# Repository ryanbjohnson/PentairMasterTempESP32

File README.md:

# Pentair MasterTemp ESP32 Interface

Open hardware and firmware-planning repository for a draft ESP32-based operating-control interface for the Pentair MasterTemp 125 heater family.

This project is early-stage engineering work. It is not a finished product, not certified, and not approved for connection to a live gas appliance.

## Safety First

- Read [DISCLAIMER.md](DISCLAIMER.md) before using any design file in this repository.
- Do not route or apply line voltage on this PCB.
- Do not add any ESP32-controlled gas-valve output.
- Preserve the OEM ignition control module and its sequencing.
- Keep the heat-request path fail-open with two normally-open relay contacts in series unless a qualified safety review approves a different architecture.
- Treat Wi-Fi, MQTT, Home Assistant, and firmware commands as advisory only. They must never override safety faults.
- A qualified technician and controls/electrical safety reviewer must approve any live-heater test.

## Current Status

The repository currently contains a KiCad scaffold and first-pass schematic capture for major control-board blocks:

- 24 VAC power entry and low-voltage rails.
- Operating-control/ICM interface and dual relay heat-request chain.
- ESP32 supervisor, watchdog, brownout, and relay-gate contract.
- Manual-aligned safety-stack input sheet and static safety gate.
- Field verification and OEM-board photo layout notes.

Remaining work includes final schematic capture, field verification, PCB/schematic parity cleanup, routing, FMEA, bench validation, and professional safety review.

## Repository Map

- `MasterTemp_ESP32_Interface_Preliminary_Design.md`: top-level design intent and safety boundary.
- `pcb/mastertemp_esp32/`: KiCad project.
- `pcb/mastertemp_esp32/docs/`: design notes, manual review, field verification, and layout notes.
- `pcb/mastertemp_esp32/references/`: project-local manuals and visual references used during review.
- `pcb/requirements/`: machine-readable requirements.
- `scripts/`: headless KiCad and test automation.
- `tests/`: scaffold and safety-boundary regression tests.

## Development Quick Start

Install KiCad 8 and Python 3, or use the included dev container.

Run checks:

```bash
./scripts/run-tests.sh
./scripts/kicad-check.sh
```

Open the KiCad project:

```bash
pcb/mastertemp_esp32/mastertemp_esp32.kicad_pro
```

Generated outputs go in ignored `reports/` and `fab/` directories.

## Contributing

Read [CONTRIBUTING.md](CONTRIBUTING.md) before opening issues or pull requests. Contributions that weaken the safety boundary, directly drive the gas valve, add line-voltage routing, or bypass the OEM ignition control module will not be accepted.

Useful first contributions:

- Improve field-verification checklists and documentation.
- Capture missing schematic detail with clear review stubs where assumptions remain open.
- Reduce ERC/DRC/parity issues without masking safety problems.
- Improve tests that enforce the safety boundary.
- Review connector pinout assumptions against installed-heater evidence.

## Security And Safety Reports

Report safety or security issues using GitHub private vulnerability reporting when available, or follow [SECURITY.md](SECURITY.md). Do not publish exploit steps, unsafe bypass instructions, or live-appliance test procedures in public issues.

## License

This repository is licensed under the MIT License. See [LICENSE](LICENSE).

Before first public hardware release, the project owner may choose to move hardware design files to a hardware-specific license such as CERN-OHL-S-2.0; see [docs/licensing.md](docs/licensing.md).

## Publishing Checklist

Before making the repository public or tagging a release, review [docs/open_source_release_checklist.md](docs/open_source_release_checklist.md).

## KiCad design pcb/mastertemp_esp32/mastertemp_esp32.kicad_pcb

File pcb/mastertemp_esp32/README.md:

# MasterTemp ESP32 KiCad Scaffold

This folder is the KiCad project area for the MasterTemp 125 ESP32 interface board.

The current files are a scaffold, not a completed schematic or board layout. The design intent and safety constraints live in:

- `../../MasterTemp_ESP32_Interface_Preliminary_Design.md`
- `../requirements/mastertemp_esp32_requirements.yaml`

Installed-heater inputs required before electrical release are tracked in `docs/field_input_verification.md`.

The original Pentair board photo reference is tracked in `docs/oem_board_photo_layout_notes.md`; save the image itself as `references/images/original_pentair_control_board_front.jpg` when exporting the chat/IDE attachment.

## Recommended workflow

1. Open `mastertemp_esp32.kicad_pro` in KiCad.
2. Immediately save the project from KiCad once, so your installed KiCad version normalizes the project metadata.
3. Work sheet by sheet, starting with `sheets/power_24vac.kicad_sch`.
4. After each sheet-level change, run ERC.
5. After placement/routing changes, run DRC.
6. Keep all project-local symbols in `libraries/symbols/mastertemp_esp32.kicad_sym`.
7. Keep all project-local footprints in `libraries/footprints/mastertemp_esp32.pretty`.

## Safety notes

- This project is an operating-control interface only.
- Do not add any ESP32-controlled gas-valve output.
- Do not route line voltage on this PCB.
- Preserve the OEM ignition control module and its sequencing.
- The heat-request output must remain dual normally-open relay contacts in series unless a qualified safety review approves another architecture.

## Folder map

- `sheets/`: hierarchical schematic sheets.
- `libraries/`: project-local symbols and footprints.
- `rules/`: layout constraints and DRC notes.
- `docs/`: design workflow notes, pin maps, and review records.
- `references/`: project-local manuals, source documents, and non-release visual references.

## Completion checklist

Use this as the live gate list for moving from scaffold to a reviewable PCB package. Keep each checkbox honest: complete means captured, checked, and reviewed, not merely started.

### Project setup

- [x] KiCad project scaffold exists with root schematic, child sheets, PCB file, local library tables, and scripts.
- [x] Four-layer board scaffold exists with preliminary 160 mm x 100 mm outline and functional placement zones.
- [x] PCB floorplan v0 exists with connector, relay, power, ESP32, analog, and test-pad placement envelopes.
- [x] Local MasterTemp 125 Rev C PDF electrical pages were reviewed and summarized in `docs/mastertemp125_rev_c_manual_review.md`.
- [x] Candidate sourced BOM and first-pass footprint placement exist for control-board circuitry.
- [x] PCB-side draft nets and first-pass relay contact-chain routing are applied and documented.
- [x] Headless KiCad `ERC` and `DRC` automation runs in the dev container.
- [x] Repository-level scaffold tests exist under `tests/`.
- [ ] KiCad project metadata has been opened and normalized once in the target GUI KiCad version.
- [ ] Generated `reports/` and `fab/` outputs are regenerated from the final release candidate.

### Inputs to close before electrical release

- [ ] Exact MasterTemp 125 model revision, serial/date range, and connected/non-connected variant are recorded.
- [ ] Field input verification record is complete and reviewed in `docs/field_input_verification.md`.
- [x] Rev C manual connector groups are reflected in draft requirements and floorplan.
- [ ] Heater harness pinout is verified from the installed unit and matching manual revision.
- [ ] 24 VAC transformer no-load and loaded voltages are measured.
- [ ] Water thermistor resistance curve is confirmed.
- [ ] Stack flue sensor electrical type and valid/fault ranges are confirmed.
- [ ] Enclosure, mounting holes, standoff height, cable-entry direction, and service clearances are selected.
- [ ] Certification/review path is chosen, including current applicable pool-heater and automatic-control standards.

### Schematic capture

- [ ] `power_24vac`: connector, fuse/PTC, MOV/TVS, bridge, VRAW bulk, 5 V supply, 3.3 V supply, power-good/brownout.
- [ ] `icm_interface`: manual-aligned operating-control connector, dual series normally-open relay contacts, coil drivers, flyback, AC opto sense, TH feedback, ICM terminal reference.
- [ ] `esp32_supervisor`: ESP32 module, programming header, watchdog, reset supervisor, I2C, relay-enable logic.
- [ ] `safety_inputs`: Fireman's Switch, PS, HLS, ES1, AGS static chain, AFS dynamic monitor, dry-contact isolated sense.
- [ ] `thermistor_sfs`: first-pass ADC/window-comparator architecture captured; final thermistor/SFS values and thresholds remain field-open.
- [ ] `ui_remote`: Pool/Common/Spa external-control dry-contact sense only; keypad/display/buzzer/status LED design remains out of scope.
- [ ] ERC has zero unreviewed violations after each sheet is captured.
- [ ] All symbols have footprints assigned or documented as no-fit/test-only.

### Safety review

- [ ] OEM ignition control module remains responsible for ignition, flame proving, and gas-valve sequencing.
- [ ] No ESP32 or board output can directly energize the gas valve.
- [ ] No line-voltage nets, connectors, labels, or routing exist on this PCB.
- [ ] Two normally-open relay contacts are in series in the `TH` heat-request path.
- [ ] Relay drive drops out on ESP32 reset, watchdog timeout, brownout, firmware fault, OTA, static safety open, invalid sensor, and relay feedback fault.
- [ ] AFS is treated as a dynamic airflow-proving input, not as a static pre-fire interlock.
- [ ] Preliminary FMEA covers welded relay, optocoupler failure, stuck ADC, brownout oscillation, firmware deadlock, and miswire cases.

### PCB layout

- [x] First-pass placement envelopes follow the zone plan in `rules/layout_constraints.md`.
- [x] Draft connector envelopes follow Rev C Figure 24 operating-control groups.
- [x] Candidate footprints are placed according to first-pass sourced part numbers.
- [x] Critical relay contact-chain PCB nets are named and first-pass routed.
- [ ] Footprints are synchronized to final schematic symbols and netlist.
- [x] ESP32 antenna keepout has no copper, components, or nearby metal-obstructing placement in the draft placement.
- [ ] Relay contact and 24 VAC control paths use assigned net classes and visible separation from logic.
- [ ] Field-side optocoupler pins face connectors and logic-side pins face MCU/expander circuitry.
- [ ] Thermistor/SFS analog traces avoid relay coils, AC sense, ESD discharge paths, and buck switch nodes.
- [x] Test pads exist for `VRAW`, `+5V`, `+3V3`, watchdog, safety chain, relay coils, TH feedback, and VAL sense.
- [x] Silkscreen warnings are present and readable.
- [x] DRC has zero unreviewed violations and schematic parity passes for the current draft.

### Fabrication and validation

- [ ] Schematic PDF, PCB plots, Gerbers, drill files, BOM, and placement outputs are generated.
- [ ] Bench test procedure is executed with an isolated 24 VAC transformer.
- [ ] Every required heat-request drop-out case is tested and recorded.
- [ ] Relay feedback/welded-contact detection is tested.
- [ ] `VAL` sense-only behavior is tested.
- [ ] 24-hour relay/sensor soak test is completed.
- [ ] Qualified technician review is complete before any live-heater connection.

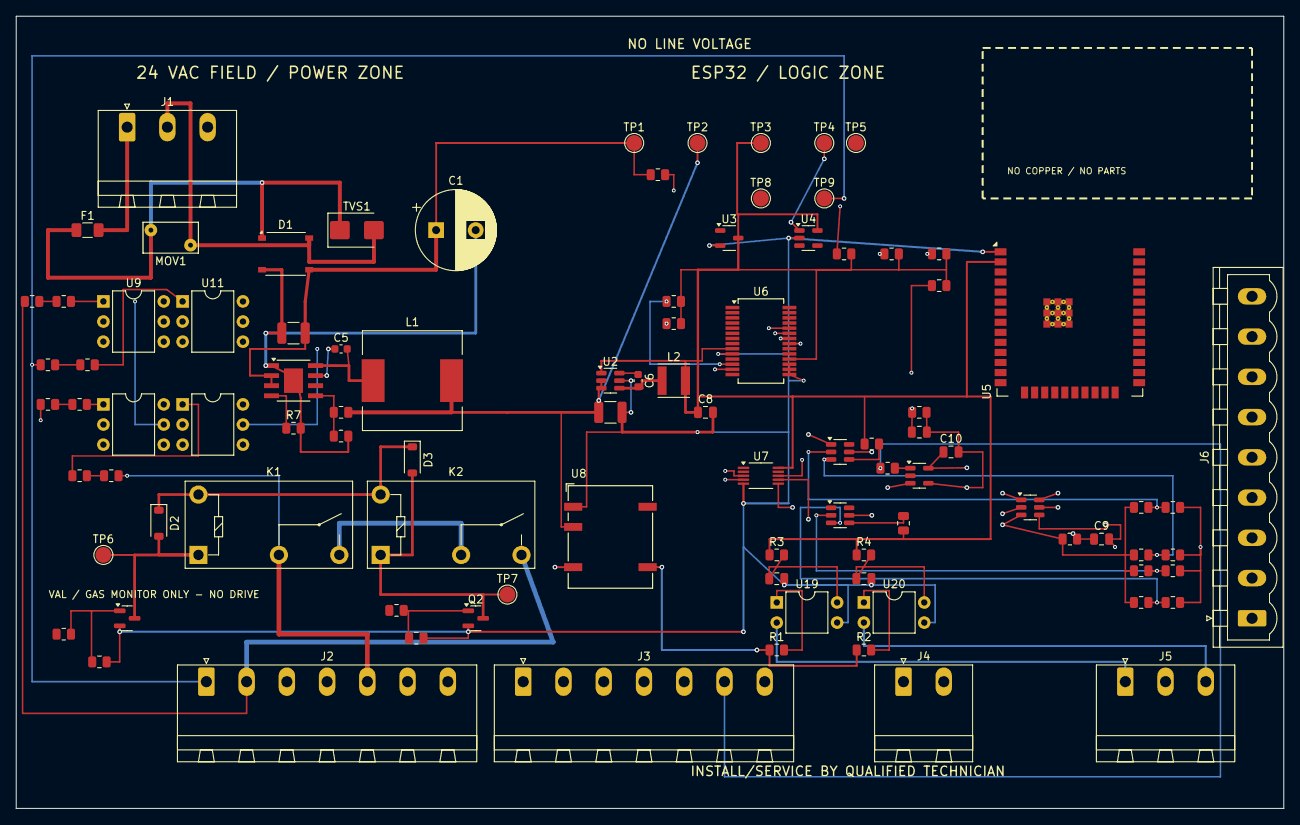
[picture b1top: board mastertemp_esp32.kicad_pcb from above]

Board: 4 copper layers, 160.0 x 100.0 mm, 95 parts (0 on the bottom side), 64 nets.

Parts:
C1: 470uF_63V; CP_Radial_D10.0mm_P5.00mm
C2, C3: 100nF_REMOTE_FILTER_TBD; C_0805_2012Metric
C4: 2.2uF_100V_VRAW_IN_TBD; C_1210_3225Metric
C5: 2.2nF_50V_BST_5V; C_0603_1608Metric
C6: 100nF_BST_3V3; C_0603_1608Metric
C7: 10uF_50V_3V3_IN_TBD; C_1210_3225Metric
C8: 22uF_10V_3V3_OUT_TBD; C_0805_2012Metric
C9: THERM_ADC_FILTER_TBD; C_0805_2012Metric
C10: SFS_ADC_FILTER_TBD; C_0805_2012Metric
C11: VRAW_MON_FILTER_TBD; C_0805_2012Metric
D1: MB10S; Diode_Bridge_Vishay_MBLS
D2: K1_FLYBACK_TBD; D_SOD-123
D3: K2_FLYBACK_TBD; D_SOD-123
F1: 0.5A_FUSE; Fuse_1206_3216Metric
J1: 24VAC_IN; PhoenixContact_MSTBA_2,5_3-G-5,08_1x03_P5.08mm_Horizontal
J2: OPERATING_CONTROL; PhoenixContact_MSTBA_2,5_7-G-5,08_1x07_P5.08mm_Horizontal
J3: SAFETY_STACK; PhoenixContact_MSTBA_2,5_7-G-5,08_1x07_P5.08mm_Horizontal
J4: THERMISTOR; PhoenixContact_MSTBA_2,5_2-G-5,08_1x02_P5.08mm_Horizontal
J5: EXT_CONTROL; PhoenixContact_MSTBA_2,5_3-G-5,08_1x03_P5.08mm_Horizontal
J6: MEMBRANE_REF; PhoenixContact_MSTBVA_2,5_9-G-5,08_1x09_P5.08mm_Vertical
K1, K2: G5Q-1A-DC5; Relay_SPST_Omron-G5Q-1A
L1: 68uH; L_12x12mm_H8mm
L2: 2.2uH; L_Vishay_IFSC-1515AH_4x4x1.8mm
MOV1: V47ZA1P; RV_Disc_D7mm_W3.9mm_P5mm
Q1, Q2: AO3400A; SOT-23
R1, R2: 2.2k_REMOTE_WET_TBD; R_0805_2012Metric
R3, R4: 10k_REMOTE_PULLUP; R_0805_2012Metric
R5: RFB5V_TOP_TBD; R_0805_2012Metric
R6: RFB5V_BOT_TBD; R_0805_2012Metric
R7: RON5V_TBD; R_0805_2012Metric
R8: VAL_OPTO_LIMIT_A_TBD; R_0805_2012Metric
R9: VAL_OPTO_LIMIT_B_TBD; R_0805_2012Metric
R10: K1_GATE_PULLDOWN_TBD; R_0805_2012Metric
R11: K2_GATE_PULLDOWN_TBD; R_0805_2012Metric
R12: VAL_OPTO_PULLUP_TBD; R_0805_2012Metric
R13: TH_OPTO_LIMIT_A_TBD; R_0805_2012Metric
R14: TH_OPTO_LIMIT_B_TBD; R_0805_2012Metric
R15: TH_OPTO_PULLUP_TBD; R_0805_2012Metric
R16: IND_OPTO_LIMIT_A_TBD; R_0805_2012Metric
R17: IND_OPTO_LIMIT_B_TBD; R_0805_2012Metric
R18: IND_OPTO_PULLUP_TBD; R_0805_2012Metric
R19: VAC24_OPTO_LIMIT_A_TBD; R_0805_2012Metric
R20: VAC24_OPTO_LIMIT_B_TBD; R_0805_2012Metric
R21: VAC24_OPTO_PULLUP_TBD; R_0805_2012Metric
R22: K1_GATE_SERIES_TBD; R_0805_2012Metric
R23: K2_GATE_SERIES_TBD; R_0805_2012Metric
R24: THERM_PULLUP_TBD; R_0805_2012Metric
R25: I2C_SDA_PULLUP_TBD; R_0805_2012Metric
R26: I2C_SCL_PULLUP_TBD; R_0805_2012Metric
R27: SFS_INPUT_SERIES_TBD; R_0805_2012Metric
R28: VRAW_MON_TOP_TBD; R_0805_2012Metric
R29: VRAW_MON_BOT_TBD; R_0805_2012Metric
R30: THERM_RANGE_OK_PULLUP_TBD; R_0805_2012Metric
R31: SFS_RANGE_OK_PULLUP_TBD; R_0805_2012Metric
R32: THERM_LOW_REF_TOP_TBD; R_0805_2012Metric
R33: THERM_LOW_REF_BOT_TBD; R_0805_2012Metric
R34: THERM_HIGH_REF_TOP_TBD; R_0805_2012Metric
R35: THERM_HIGH_REF_BOT_TBD; R_0805_2012Metric
R36: SFS_LOW_REF_TOP_TBD; R_0805_2012Metric
R37: SFS_LOW_REF_BOT_TBD; R_0805_2012Metric
R38: SFS_HIGH_REF_TOP_TBD; R_0805_2012Metric
R39: SFS_HIGH_REF_BOT_TBD; R_0805_2012Metric
TP1: VRAW; TestPoint_Pad_D2.0mm
TP2: +5V; TestPoint_Pad_D2.0mm
TP3: +3V3; TestPoint_Pad_D2.0mm
TP4: WATCHDOG_OK; TestPoint_Pad_D2.0mm
TP5: SAFETY_STATIC_OK; TestPoint_Pad_D2.0mm
TP6: K1_COIL; TestPoint_Pad_D2.0mm
TP7: K2_COIL; TestPoint_Pad_D2.0mm
TP8: TH_FEEDBACK; TestPoint_Pad_D2.0mm
TP9: VAL_SENSE; TestPoint_Pad_D2.0mm
TVS1: SMBJ51CA; D_SMB
U1: LM5164DDAR; TI_SO-PowerPAD-8
U2: AP63203WU-7; TSOT-23-6
U3: TPS3839G33DBZR; SOT-23-3
U4: TPS3823-33DBVR; SOT-23-5
U5: ESP32-WROOM-32E-N16; ESP32-WROOM-32E
U6: MCP23017-E/SS; SSOP-28_5.3x10.2mm_P0.65mm
U7: ADS1115IDGSR; VSSOP-10_3x3mm_P0.5mm
U8: NXE1S0505MC-R7; Converter_DCDC_Murata_NXExSxxxxMC_SMD
U9: H11AA1M_TH; DIP-6_W7.62mm
U10: H11AA1M_IND; DIP-6_W7.62mm
U11: H11AA1M_VAL; DIP-6_W7.62mm
U12: H11AA1M_24VAC; DIP-6_W7.62mm
U14: THERMISTOR_AFE_TBD; SOT-23-6
U16: TLV6700DDCR_THERM; SOT-23-6
U17: TLV6700DDCR_SFS; SOT-23-6
U18: OPA333AIDBVR; SOT-23-5
U19: LTV-817S_SPA_CANDIDATE; DIP-4_W7.62mm
U20: LTV-817S_POOL_CANDIDATE; DIP-4_W7.62mm

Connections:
+3V3: C8.1, L2.2, R3.1, R4.1, R12.2, R15.2, R18.2, R21.2, R25.1, R26.1, R30.1, R31.1, TP3.1, U2.1, U3.3, U4.5, U5.2, U6.9, U6.18, U7.10
+3V3_ADC: R24.1, R32.1, R34.1, R36.1, R38.1, U14.3, U18.3
+5V: C7.1, L1.2, R5.1, TP2.1, U2.2, U2.3, U8.3
+5V_RELAY: D2.1, D3.1, K1.5, K2.5
AGND: C9.2, C10.2, C11.2, R29.2, R33.2, R35.2, R37.2, R39.2, U14.4, U18.4
BST_3V3: C6.1, U2.6
BST_5V: C5.1, U1.7
COMMON_LINE: J5.2, U8.7
FB_5V_TBD: R5.2, R6.1, U1.5
GND: C2.2, C3.2, C7.2, C8.2, Q1.2, Q2.2, R10.2, R11.2, U2.5, U3.2, U4.2, U5.1, U6.10, U6.15, U6.16, U6.17, U7.5, U8.1, U9.4, U10.4, U11.4, U12.4, U16.5, U17.5, U19.3, U20.3
HEAT_CHAIN_K1_K2: K1.3, K2.2
I2C_SCL: R26.2, U6.12, U7.4
I2C_SDA: R25.2, U6.13, U7.3
ICM_24VAC_SOURCE: J2.5, K1.2, R19.1
ICM_GND_REF: J2.4, U9.2, U10.2, U11.2, U12.2
IND_OPTO_GPIO: R18.1, U6.23, U10.5
IND_OPTO_INPUT: R17.2, U10.1
IND_OPTO_LIMIT_A: R16.2, R17.1
IND_SENSE_AC: J2.3, R16.1
ISO_REMOTE_5V: R1.1, R2.1, U8.8
K1_COIL_LOW: D2.2, K1.1, Q1.3, TP6.1
K2_COIL_LOW: D3.2, K2.1, Q2.3, TP7.1
PGND_RAW: C1.2, C4.2, D1.4, R6.2, R7.2, U1.1, U1.9
POOL_LED_A: R2.2, U20.1
POOL_LINE: J5.3, U20.2
RELAY_K1_GATE: Q1.1, R10.1, R22.2
RELAY_K2_GATE: Q2.1, R11.1, R23.2
REMOTE_POOL_SENSE: C3.1, R4.2, U20.4
REMOTE_SPA_SENSE: C2.1, R3.2, U19.4
RON_5V_TBD: R7.1, U1.4
SFS_ADC: C10.1, U7.7, U18.5
SFS_FIELD_INPUT: R27.2, U18.1
SFS_HIGH_REF_TBD: R38.2, R39.1, U17.3
SFS_INPUT: J3.6, R27.1
SFS_LOW_REF_TBD: R36.2, R37.1, U17.2
SFS_RANGE_OK: R31.2, U17.4
SPA_LED_A: R1.2, U19.1
SPA_LINE: J5.1, U19.2
SW_3V3: C6.2, L2.1, U2.4
SW_5V: C5.2, L1.1, U1.8
THERMISTOR_A: J4.1, U14.1
THERMISTOR_ADC: C9.1, R24.2, U7.6, U14.5
THERMISTOR_B: J4.2, U14.2
THERMISTOR_RANGE_OK: R30.2, U16.4
THERM_HIGH_REF_TBD: R34.2, R35.1, U16.3
THERM_LOW_REF_TBD: R32.2, R33.1, U16.2
THERM_WINDOW_SENSE: U14.6, U16.1
TH_HEAT_REQUEST_OUT: J2.2, K2.3, R13.1
TH_OPTO_GPIO: R15.1, U6.22, U9.5
TH_OPTO_INPUT: R14.2, U9.1
TH_OPTO_LIMIT_A: R13.2, R14.1
VAC24_A: F1.2, J1.1
VAC24_A_FUSED: D1.1, F1.1, MOV1.1, TVS1.1
VAC24_B: D1.2, J1.2, MOV1.2, TVS1.2
VAC24_OPTO_GPIO: R21.1, U6.24, U12.5
VAC24_OPTO_INPUT: R20.2, U12.1
VAC24_OPTO_LIMIT_A: R19.2, R20.1
VAL_OPTO_GPIO: R12.1, U6.21, U11.5
VAL_OPTO_INPUT: R9.2, U11.1
VAL_OPTO_LIMIT_A: R8.2, R9.1
VAL_SENSE_AC: J2.1, R8.1, TP9.1
VRAW: C1.1, C4.1, D1.3, R28.1, TP1.1, U1.2, U1.3
VRAW_MONITOR_ADC: C11.1, R28.2, R29.1, U7.8
WATCHDOG_OK: TP4.1, U4.1

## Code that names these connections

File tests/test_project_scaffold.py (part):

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            ("U3", "3"): "+3V3",
            ("U5", "1"): "GND",
            ("U5", "2"): "+3V3",
            ("U6", "21"): "VAL_OPTO_GPIO",
            ("U6", "22"): "TH_OPTO_GPIO",
            ("U6", "23"): "IND_OPTO_GPIO",
            ("U6", "24"): "VAC24_OPTO_GPIO",
            ("R8", "1"): "VAL_SENSE_AC",
            ("R8", "2"): "VAL_OPTO_LIMIT_A",
            ("R9", "1"): "VAL_OPTO_LIMIT_A",
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            ("R13", "2"): "TH_OPTO_LIMIT_A",
            ("R14", "1"): "TH_OPTO_LIMIT_A",
            ("R14", "2"): "TH_OPTO_INPUT",
            ("R15", "1"): "TH_OPTO_GPIO",
            ("R15", "2"): "+3V3",
            ("U9", "1"): "TH_OPTO_INPUT",
            ("U9", "2"): "ICM_GND_REF",
            ("U9", "4"): "GND",
            ("U9", "5"): "TH_OPTO_GPIO",
            ("R16", "1"): "IND_SENSE_AC",
            ("R16", "2"): "IND_OPTO_LIMIT_A",
            ("R17", "1"): "IND_OPTO_LIMIT_A",
            ("R17", "2"): "IND_OPTO_INPUT",
            ("R18", "1"): "IND_OPTO_GPIO",
            ("R18", "2"): "+3V3",
            ("U10", "1"): "IND_OPTO_INPUT",
            ("U10", "2"): "ICM_GND_REF",
            ("U10", "4"): "GND",
            ("U10", "5"): "IND_OPTO_GPIO",
            ("R19", "1"): "ICM_24VAC_SOURCE",
            ("R19", "2"): "VAC24_OPTO_LIMIT_A",
            ("R20", "1"): "VAC24_OPTO_LIMIT_A",
            ("R20", "2"): "VAC24_OPTO_INPUT",
            ("R21", "1"): "VAC24_OPTO_GPIO",
            ("R21", "2"): "+3V3",
            ("U12", "1"): "VAC24_OPTO_INPUT",
            ("U12", "2"): "ICM_GND_REF",
            ("U12", "4"): "GND",
            ("U12", "5"): "VAC24_OPTO_GPIO",
            ("U11", "1"): "VAL_OPTO_INPUT",
            ("U11", "2"): "ICM_GND_REF",
            ("U11", "4"): "GND",
            ("U11", "5"): "VAL_OPTO_GPIO",
            ("R10", "1"): "RELAY_K1_GATE",
            ("R10", "2"): "GND",
            ("R11", "1"): "RELAY_K2_GATE",
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            ("C11", "1"): "VRAW_MONITOR_ADC",
            ("C11", "2"): "AGND",
            ("U7", "8"): "VRAW_MONITOR_ADC",
            ("R12", "1"): "VAL_OPTO_GPIO",
            ("R12", "2"): "+3V3",
            ("Q1", "2"): "GND",
            ("Q2", "2"): "GND",
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            "K1_COIL_LOW", "K2_COIL_LOW", "REMOTE_SPA_SENSE", "REMOTE_POOL_SENSE",
            "SPA_LINE", "POOL_LINE", "ISO_REMOTE_5V",
            "SPA_LED_A", "POOL_LED_A", "WATCHDOG_OK", "VAL_SENSE_AC",
            "VAL_OPTO_LIMIT_A", "VAL_OPTO_INPUT", "ICM_GND_REF", "VAL_OPTO_GPIO",
            "TH_OPTO_LIMIT_A", "TH_OPTO_INPUT", "TH_OPTO_GPIO",
            "IND_SENSE_AC", "IND_OPTO_LIMIT_A", "IND_OPTO_INPUT", "IND_OPTO_GPIO",
            "VAC24_OPTO_LIMIT_A", "VAC24_OPTO_INPUT", "VAC24_OPTO_GPIO",
            "RELAY_K1_GATE", "RELAY_K2_GATE",
            "+3V3_ADC", "AGND", "THERMISTOR_ADC",
            "I2C_SDA", "I2C_SCL",
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
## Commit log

2026-05-31 Requirements
2026-05-31 AI gen
2026-05-31 Starting design
2026-06-01 Bump
2026-06-01 Make open source.
